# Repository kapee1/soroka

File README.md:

# soroka - DIY-Friendly 40% keyboard

### Build guide [[EN]](https://github.com/kapee1/soroka/blob/main/build%20guides/Soroka%20v2%20Build%20guide%20%5BEN%5D.md) | [[RU]](https://github.com/kapee1/soroka/blob/main/build%20guides/Soroka%20v2%20Build%20guide%20%5BRU%5D.md)

__Parts for v1 and v2 are not compatible!__

### Main features:

* Easy to build. Great for soldering practice.
* Supports all cyrillic symbols in base layer.
* Compatible with most base-kit keycap sets. No 40s addons needed.
* Optional Panasonic EVQWGD001 or EC-11 encoder
* Plate also optional. You can build keyboard without a plate to reduce cost.
* Variable bottom-row with a 3u spacebars support.
* Customizable magnet panels
* VIAL/QMK/[ZMK Firmware](https://github.com/aroum/zmk-soroka) by [aroum](https://github.com/aroum)
* *NEW!* Hotswap PCB (untested, but should be fine). Hotswap PCB uses different diodes. Please check the BOM file at the end of this README file.

### Layout:

### Sizes:

## Hotswap PCB BOM (Be careful, it's still untested!)
| Part     | Quantity |
|----------|----------|
| Soroka PCB (HS)   | 1   | 
| RP2040-Zero (unsoldered pins) | 1   |
| Any MX Hotswap Sockets | 52   |
| BAT54C, SOT-23 Diodes  |  27 | 
| Panasonic EVQWGD001 (optional) or EC-11 Encoder | 1   |  

## Soldered PCB BOM
| Part     | Quantity |
|----------|----------|
| Soroka PCB (Soledered)   | 1   | 
| RP2040-Zero (unsoldered pins) | 1   | 
| 1N4148w SOD-123 Diodes        | 50  | 
| Panasonic EVQWGD001 (optional) or EC-11 Encoder | 1   |  

## Assembly BOM:
| Part     | Quantity |
|----------|----------|
| Soroka PCB (Soldered or Hotswap)   | 1   | 
| Soroka Plate (Optional)       | 1   | 
| Soroka Case                   | 1   | 
| Soroka Panel                  | 1   | 
| Soroka Spacer                 | 1   | 
| Oval feets 22x4x1.5mm         | 4   |  
| Silicone washers 2x5x1        | 9   |
| M2 x 4mm Screws               | 13  |  
| M2 Inserts 3mm (OD3.2)        | 13  |  
| Round magnets 3x1 mm          | 8   | 

In case of cover with screws, you don't need spacer and magnets, but you will need:

| Part     | Quantity |
|----------|----------|
| M2 x 5 mm Screws                       | 8  |  
| M2 Brass Standoffs Female-Female 11 mm | 4  |

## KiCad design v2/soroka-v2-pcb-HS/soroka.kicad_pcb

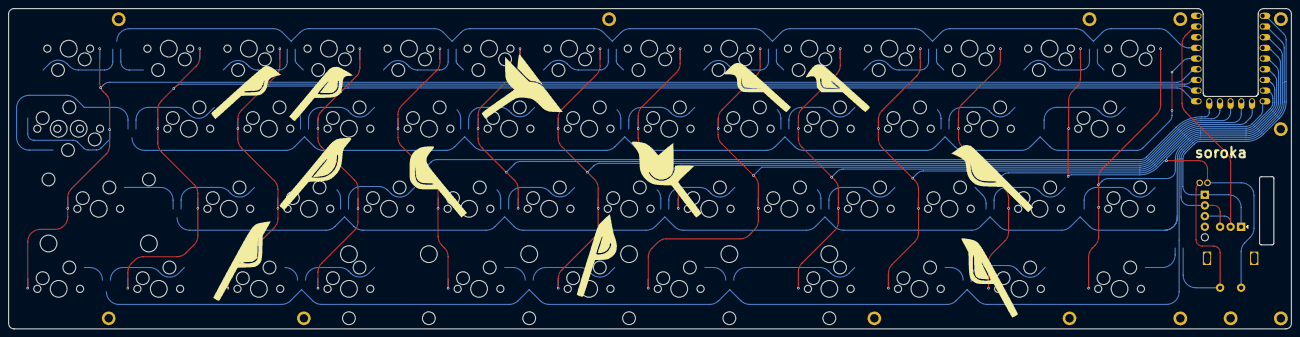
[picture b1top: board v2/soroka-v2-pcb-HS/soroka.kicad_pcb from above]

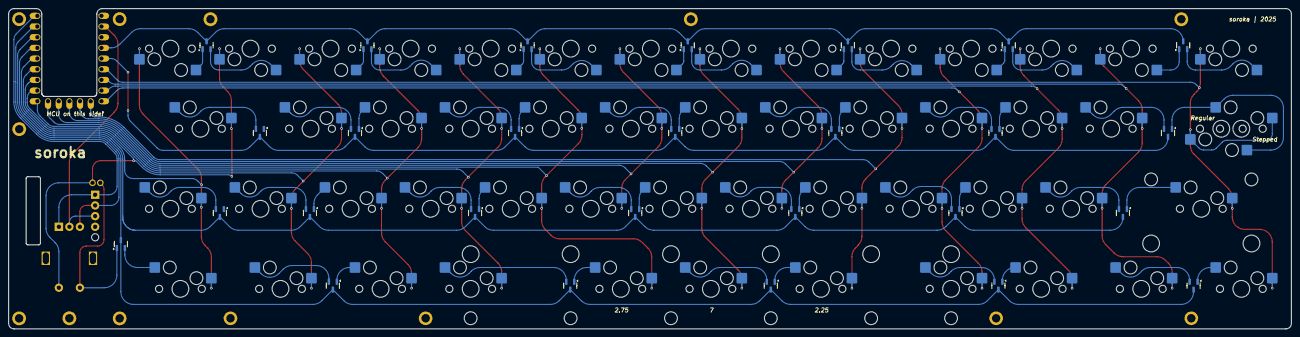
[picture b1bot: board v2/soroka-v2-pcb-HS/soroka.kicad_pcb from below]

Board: 2 copper layers, 305.2 x 76.2 mm, 83 parts (27 on the bottom side), 73 nets.

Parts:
D1, D2, D3, D4, D5, D6, D7, D8, D9, D10, D11, D12, D13, D14, D15, D16, D17, D18, D19, D20, D21, D22, D23, D24, D25, D26, D27: BAT54C; SOT-23
MP: (no value)
RZ1: RP2040-Zero; MCU_rp2040-zero-tht
SW1: MX150H
SW2, SW3, SW4, SW5, SW6, SW7, SW8, SW9, SW10, SW11, SW12, SW13, SW14, SW16, SW17, SW18, SW19, SW20, SW21, SW22, SW23, SW24, SW25, SW26, SW29, SW30, SW31, SW32, SW33, SW34, SW35, SW36, SW37, SW38, SW45, SW50: MXSwitch; MX100H
SW15: Normal; MX125H
SW27: MX175H
SW28: MX225R; MX225H
SW39: 1.25u; MX125H
SW41: 1u; MX100H
SW42, SW43, SW44, SW51, SW52, SW53: MXH125; MX125H
SW46: Stepped; MX175H
SW47: 2.25u; MX225HR
SW48: 7u; MX700HR
SW54: 2.75u; MX275HR
SW55: RotaryEncoder_Switch; RotaryEncoder_Alps_EC11E-Switch_Vertical_H20mm
SW56: RotaryEncoder_Switch; EVQWGD001

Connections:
COL0: RZ1.18 (GP27), SW1.2 (Row), SW15.2 (Row), SW28.2 (Row), SW42.2 (Row), SW46.2 (Row)
COL1: RZ1.17 (GP26), SW2.2 (Row), SW16.2 (Row), SW29.2 (Row), SW43.2 (Row)
COL2: RZ1.16 (GP15), SW3.2 (Row), SW17.2 (Row), SW30.2 (Row), SW44.2 (Row)
COL3: RZ1.15 (GP14), SW4.2 (Row), SW18.2 (Row), SW31.2 (Row), SW45.2 (Row)
COL4: RZ1.14 (GP13), SW5.2 (Row), SW19.2 (Row), SW32.2 (Row), SW47.2 (Row)
COL5: RZ1.13 (GP12), SW6.2 (Row), SW20.2 (Row), SW33.2 (Row)
COL6: RZ1.12 (GP11), SW7.2 (Row), SW21.2 (Row), SW34.2 (Row), SW48.2 (Row)
COL7: RZ1.11 (GP10), SW8.2 (Row), SW22.2 (Row), SW35.2 (Row)
COL8: RZ1.10 (GP9), SW9.2 (Row), SW23.2 (Row), SW36.2 (Row), SW54.2 (Row)
COL9: RZ1.9 (GP8), SW10.2 (Row), SW24.2 (Row), SW37.2 (Row), SW50.2 (Row)
COL10: RZ1.8 (GP7), SW11.2 (Row), SW25.2 (Row), SW38.2 (Row), SW51.2 (Row)
COL11: RZ1.7 (GP6), SW12.2 (Row), SW26.2 (Row), SW39.2 (Row), SW52.2 (Row)
COL12: RZ1.6 (GP5), SW13.2 (Row), SW27.2 (Row), SW55.S2, SW56.S2
COL13: RZ1.5 (GP4), SW14.2 (Row), SW41.2 (Row), SW53.2 (Row)
ENC_CCW: RZ1.1 (GP0), SW55.A, SW56.A
ENC_CW: RZ1.2 (GP1), SW55.B, SW56.B
GND: RZ1.22 (GND), SW55.C, SW56.C
unnamed: D24.1, SW55.S1, SW56.S1
unnamed: D1.2, SW1.1 (Col)
unnamed: D1.1, SW2.1 (Col)
unnamed: D2.2, SW3.1 (Col)
unnamed: D2.1, SW4.1 (Col)
unnamed: D3.2, SW5.1 (Col)
unnamed: D3.1, SW6.1 (Col)
unnamed: D4.2, SW7.1 (Col)
unnamed: D4.1, SW8.1 (Col)
unnamed: D5.2, SW9.1 (Col)
unnamed: D5.1, SW10.1 (Col)
unnamed: D6.2, SW11.1 (Col)
unnamed: D6.1, SW12.1 (Col)
unnamed: D7.2, SW13.1 (Col)
unnamed: D7.1, SW14.1 (Col)
unnamed: D8.1, SW15.1 (Col), SW46.1 (Col)
unnamed: D8.2, SW16.1 (Col)
unnamed: D9.1, SW17.1 (Col)
unnamed: D9.2, SW18.1 (Col)
unnamed: D10.1, SW19.1 (Col)
unnamed: D10.2, SW20.1 (Col)
unnamed: D11.1, SW21.1 (Col)
unnamed: D11.2, SW22.1 (Col)
unnamed: D12.1, SW23.1 (Col)
unnamed: D12.2, SW24.1 (Col)
unnamed: D13.1, SW25.1 (Col)
unnamed: D13.2, SW26.1 (Col)
unnamed: D14.2, SW27.1 (Col)
unnamed: D15.1, SW28.1 (Col)
unnamed: D15.2, SW29.1 (Col)
unnamed: D16.1, SW30.1 (Col)
unnamed: D16.2, SW31.1 (Col)
unnamed: D17.1, SW32.1 (Col)
unnamed: D17.2, SW33.1 (Col)
unnamed: D18.1, SW34.1 (Col)
unnamed: D18.2, SW35.1 (Col)
unnamed: D19.1, SW36.1 (Col)
unnamed: D19.2, SW37.1 (Col)
unnamed: D20.1, SW38.1 (Col)
unnamed: D20.2, SW39.1 (Col)
unnamed: D21.2, SW41.1 (Col)
unnamed: D22.1, SW42.1 (Col)
unnamed: D22.2, SW43.1 (Col)
unnamed: D23.1, SW44.1 (Col)
unnamed: D23.2, SW45.1 (Col)
unnamed: D27.1, SW47.1 (Col)
unnamed: D27.2, SW48.1 (Col)
unnamed: D26.2, SW50.1 (Col)
unnamed: D25.1, SW51.1 (Col)
unnamed: D25.2, SW52.1 (Col)
unnamed: D24.2, SW53.1 (Col)
unnamed: D26.1, SW54.1 (Col)
ROW0: D1.3, D2.3, D3.3, D4.3, D5.3, D6.3, D7.3, RZ1.20 (GP29)
ROW1: D8.3, D9.3, D10.3, D11.3, D12.3, D13.3, D14.3, RZ1.19 (GP28)
ROW2: D15.3, D16.3, D17.3, D18.3, D19.3, D20.3, D21.3, RZ1.4 (GP3)
ROW3: D22.3, D23.3, D24.3, D25.3, D26.3, D27.3, RZ1.3 (GP2)

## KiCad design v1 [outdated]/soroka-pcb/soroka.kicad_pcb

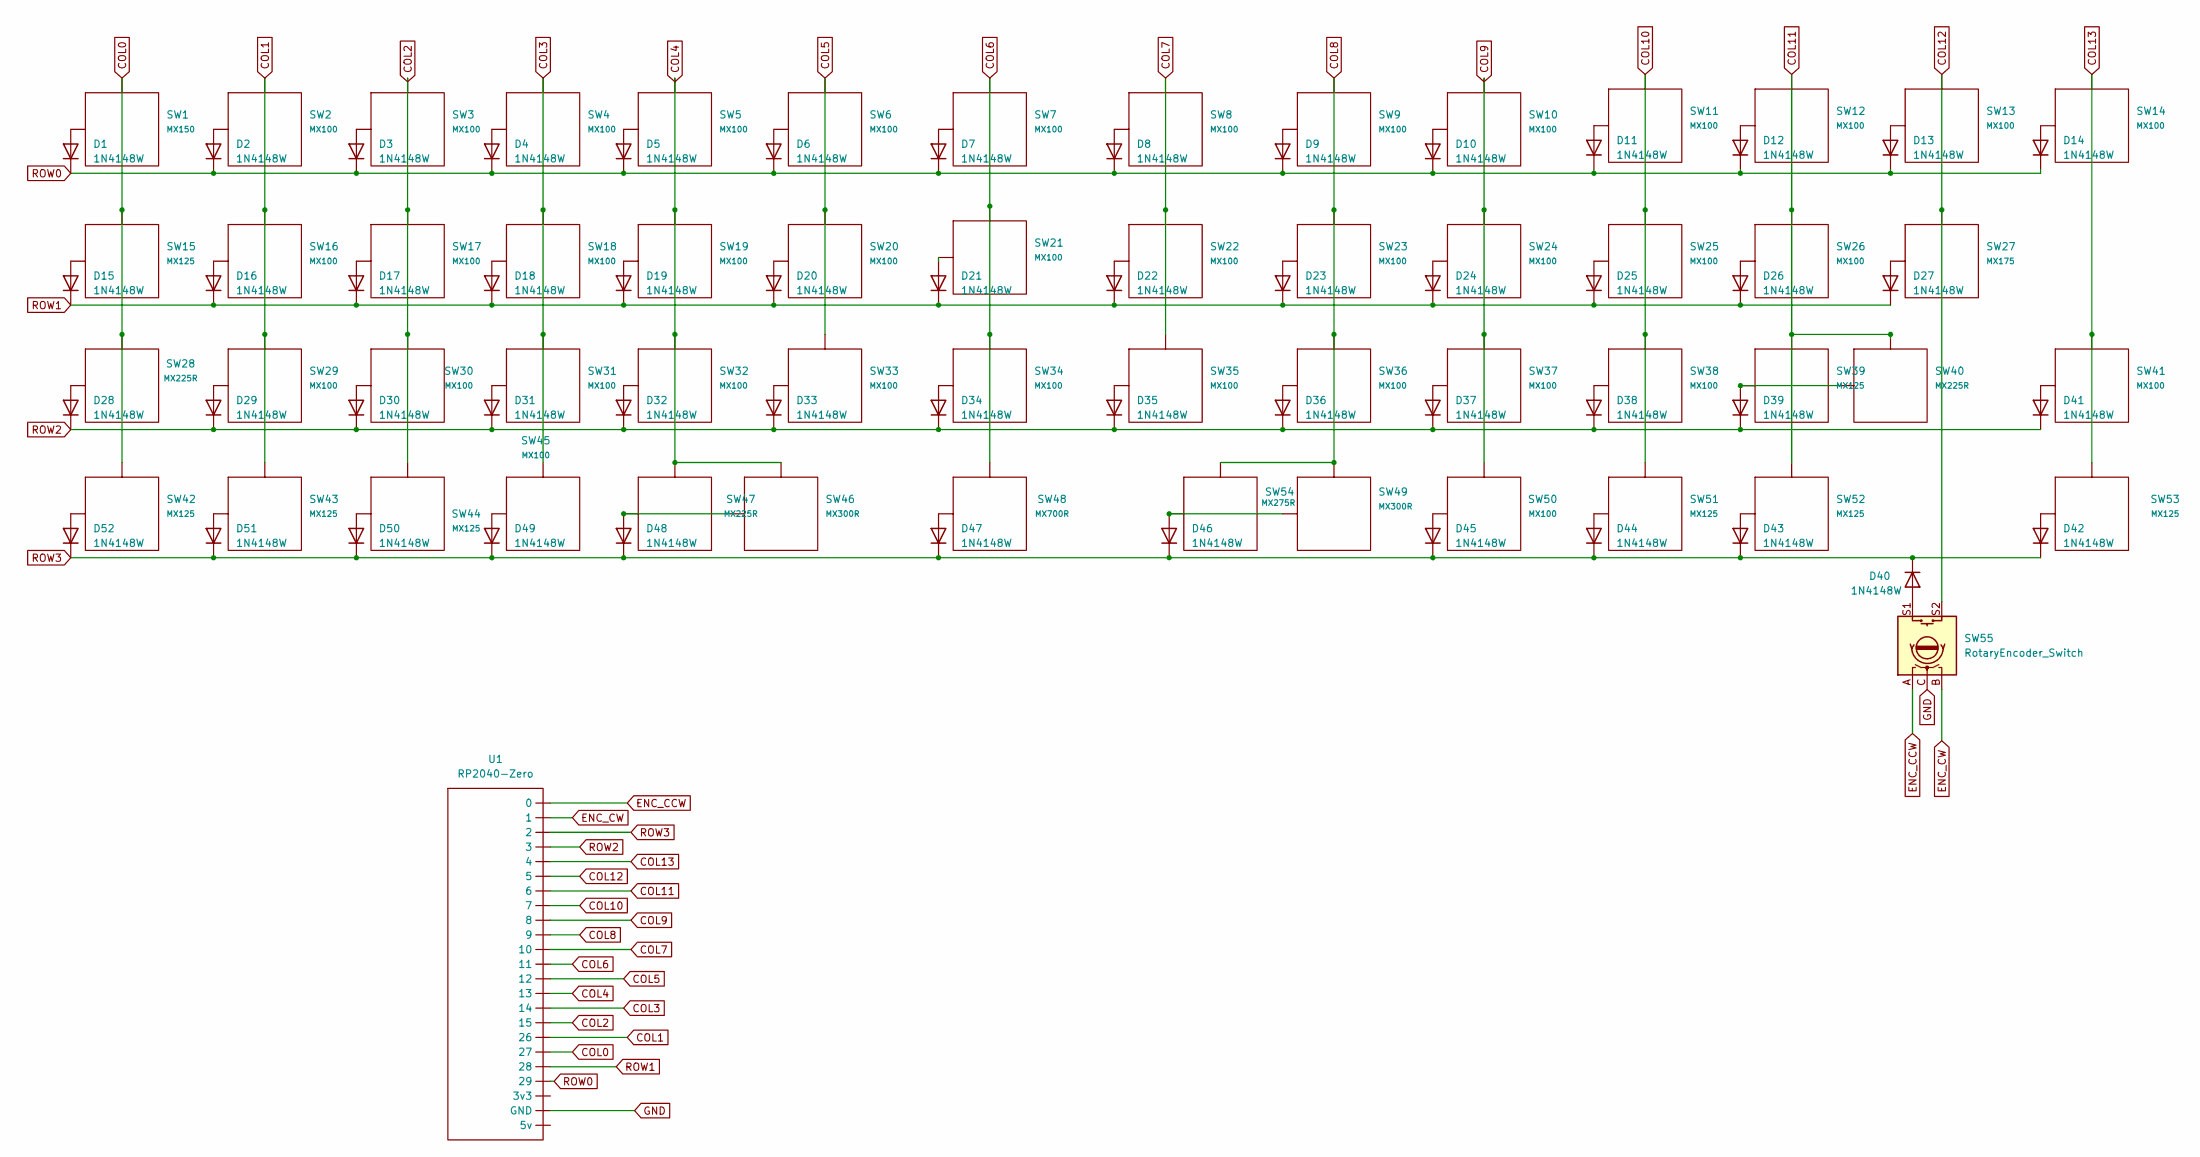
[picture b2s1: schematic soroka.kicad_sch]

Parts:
D1, D2, D3, D4, D5, D6, D7, D8, D9, D10, D11, D12, D13, D14, D15, D16, D17, D18, D19, D20, D21, D22, D23, D24, D25, D26, D27, D28, D29, D30, D31, D32, D33, D34, D35, D36, D37, D38, D39, D40, D41, D42, D43, D44, D45, D46, D47, D48, D49, D50, D51, D52: 1N4148W; D_SOD-123
SW1: MX150
SW2, SW3, SW4, SW5, SW6, SW7, SW8, SW9, SW10, SW11, SW12, SW13, SW14, SW16, SW17, SW18, SW19, SW20, SW21, SW22, SW23, SW24, SW25, SW26, SW29, SW30, SW31, SW32, SW33, SW34, SW35, SW36, SW37, SW38, SW41, SW45, SW50: MX100
SW15, SW39, SW42, SW43, SW44, SW51, SW52, SW53: MX125
SW27: MX175
SW28, SW40: MX225R; MX225
SW46, SW49: MX300R
SW47: MX225R
SW48: MX700R
SW54: MX275R
SW55: RotaryEncoder_Switch; RotaryEncoder_Alps_EC11E-Switch_Vertical_H20mm
U1: RP2040-Zero; MCU_rp2040-zero-smd

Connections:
COL0: SW1.2 (Row), SW15.2 (Row), SW28.2 (Row), SW42.2 (Row), U1.27; also elsewhere on the board
COL1: SW2.2 (Row), SW16.2 (Row), SW29.2 (Row), SW43.2 (Row), U1.26
COL2: SW3.2 (Row), SW17.2 (Row), SW30.2 (Row), SW44.2 (Row), U1.15
COL3: SW4.2 (Row), SW18.2 (Row), SW31.2 (Row), SW45.2 (Row), U1.14
COL4: SW5.2 (Row), SW19.2 (Row), SW32.2 (Row), SW46.2 (Row), SW47.2 (Row), U1.13
COL5: SW6.2 (Row), SW20.2 (Row), SW33.2 (Row), U1.12
COL6: SW7.2 (Row), SW21.2 (Row), SW34.2 (Row), SW48.2 (Row), U1.11
COL7: SW8.2 (Row), SW22.2 (Row), SW35.2 (Row), U1.10
COL8: SW9.2 (Row), SW23.2 (Row), SW36.2 (Row), SW49.2 (Row), SW54.2 (Row), U1.9
COL9: SW10.2 (Row), SW24.2 (Row), SW37.2 (Row), SW50.2 (Row), U1.8
COL10: SW11.2 (Row), SW25.2 (Row), SW38.2 (Row), SW51.2 (Row), U1.7
COL11: SW12.2 (Row), SW26.2 (Row), SW39.2 (Row), SW40.2 (Row), SW52.2 (Row), U1.6
COL12: SW13.2 (Row), SW27.2 (Row), SW55.S2, U1.5
COL13: SW14.2 (Row), SW41.2 (Row), SW53.2 (Row), U1.4
ENC_CCW: SW55.A, U1.0
ENC_CW: SW55.B, U1.1
GND: SW55.C, U1.GND
unnamed: D1.2 (A), SW1.1 (Col)
unnamed: D2.2 (A), SW2.1 (Col)
unnamed: D3.2 (A), SW3.1 (Col)
unnamed: D4.2 (A), SW4.1 (Col)
unnamed: D5.2 (A), SW5.1 (Col)
unnamed: D6.2 (A), SW6.1 (Col)
unnamed: D7.2 (A), SW7.1 (Col)
unnamed: D8.2 (A), SW8.1 (Col)
unnamed: D9.2 (A), SW9.1 (Col)
unnamed: D10.2 (A), SW10.1 (Col)
unnamed: D11.2 (A), SW11.1 (Col)
unnamed: D12.2 (A), SW12.1 (Col)
unnamed: D13.2 (A), SW13.1 (Col)
unnamed: D14.2 (A), SW14.1 (Col)
unnamed 31: D15.2 (A), SW15.1 (Col); also elsewhere on the board
unnamed: D16.2 (A), SW16.1 (Col)
unnamed: D17.2 (A), SW17.1 (Col)
unnamed: D18.2 (A), SW18.1 (Col)
unnamed: D19.2 (A), SW19.1 (Col)
unnamed: D20.2 (A), SW20.1 (Col)
unnamed: D21.2 (A), SW21.1 (Col)
unnamed: D22.2 (A), SW22.1 (Col)
unnamed: D23.2 (A), SW23.1 (Col)
unnamed: D24.2 (A), SW24.1 (Col)
unnamed: D25.2 (A), SW25.1 (Col)
unnamed: D26.2 (A), SW26.1 (Col)
unnamed: D27.2 (A), SW27.1 (Col)
unnamed: D28.2 (A), SW28.1 (Col)
unnamed: D29.2 (A), SW29.1 (Col)
unnamed: D30.2 (A), SW30.1 (Col)
unnamed: D31.2 (A), SW31.1 (Col)
unnamed: D32.2 (A), SW32.1 (Col)
unnamed: D33.2 (A), SW33.1 (Col)
unnamed: D34.2 (A), SW34.1 (Col)
unnamed: D35.2 (A), SW35.1 (Col)
unnamed: D36.2 (A), SW36.1 (Col)
unnamed: D37.2 (A), SW37.1 (Col)
unnamed: D38.2 (A), SW38.1 (Col)
unnamed: D39.2 (A), SW39.1 (Col), SW40.1 (Col)
unnamed: D40.2 (A), SW55.S1
unnamed: D41.2 (A), SW41.1 (Col)
unnamed: D42.2 (A), SW53.1 (Col)
unnamed: D43.2 (A), SW52.1 (Col)
unnamed: D44.2 (A), SW51.1 (Col)
unnamed: D45.2 (A), SW50.1 (Col)
unnamed: D46.2 (A), SW49.1 (Col), SW54.1 (Col)
unnamed: D47.2 (A), SW48.1 (Col)
unnamed: D48.2 (A), SW46.1 (Col), SW47.1 (Col)
unnamed: D49.2 (A), SW45.1 (Col)
unnamed: D50.2 (A), SW44.1 (Col)
unnamed: D51.2 (A), SW43.1 (Col)
unnamed: D52.2 (A), SW42.1 (Col)
ROW0: D1.1 (K), D2.1 (K), D3.1 (K), D4.1 (K), D5.1 (K), D6.1 (K), D7.1 (K), D8.1 (K), D9.1 (K), D10.1 (K), D11.1 (K), D12.1 (K), D13.1 (K), D14.1 (K), U1.29
ROW1: D15.1 (K), D16.1 (K), D17.1 (K), D18.1 (K), D19.1 (K), D20.1 (K), D21.1 (K), D22.1 (K), D23.1 (K), D24.1 (K), D25.1 (K), D26.1 (K), D27.1 (K), U1.28
ROW2: D28.1 (K), D29.1 (K), D30.1 (K), D31.1 (K), D32.1 (K), D33.1 (K), D34.1 (K), D35.1 (K), D36.1 (K), D37.1 (K), D38.1 (K), D39.1 (K), D41.1 (K), U1.3
ROW3: D40.1 (K), D42.1 (K), D43.1 (K), D44.1 (K), D45.1 (K), D46.1 (K), D47.1 (K), D48.1 (K), D49.1 (K), D50.1 (K), D51.1 (K), D52.1 (K), U1.2

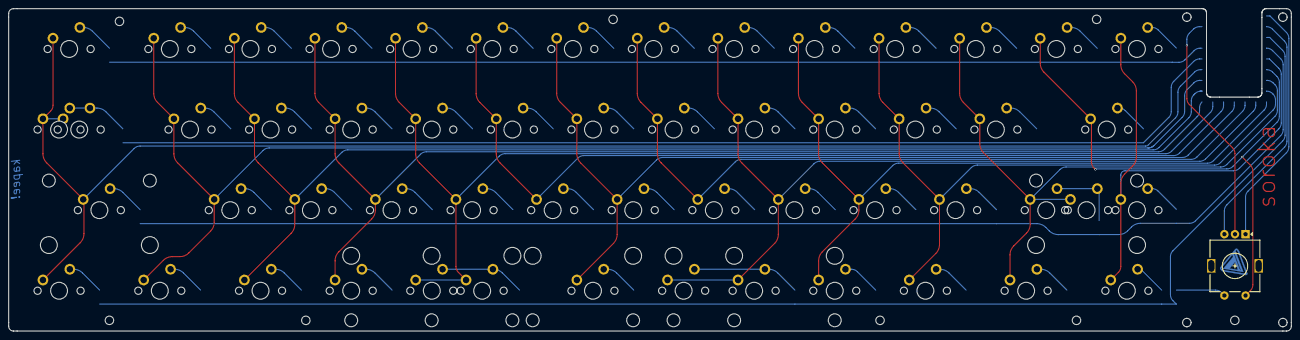
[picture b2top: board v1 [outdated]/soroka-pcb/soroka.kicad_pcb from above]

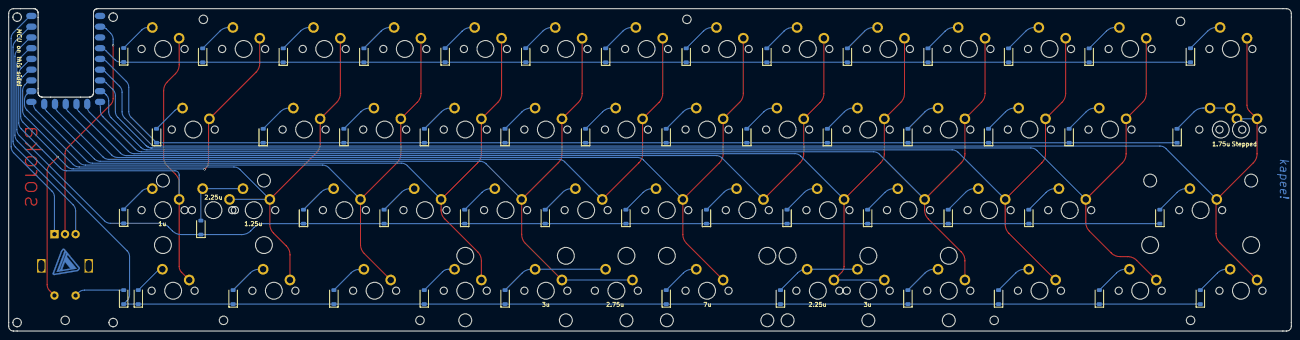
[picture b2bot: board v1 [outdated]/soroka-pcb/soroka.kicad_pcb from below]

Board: 2 copper layers, 303.2 x 76.2 mm, 109 parts (54 on the bottom side), 73 nets.

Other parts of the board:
SW55#2: 1.75u; MX175

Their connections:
COL0: SW55#2.2; also elsewhere on the board
unnamed 31: SW55#2.1; also elsewhere on the board

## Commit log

2024-01-14 added pcb, plate and case files
2024-01-14 added production files
2024-01-15 fixed typo and created new production files
2024-01-19 added 4 variant of right side panels
2024-01-22 fixed stabs cutouts
2024-01-22 added vial firmware
2024-01-29 added 6-degree case
2024-02-01 updated keymaps
2024-08-27 initial commit for v2
2024-08-27 added v2 files
2024-09-19 sorted photos
2024-09-23 added RU build guide
2024-09-23 added EN build guide
2025-04-13 added roundings for evq panels and a new panel
2025-04-13 rename folder
2025-05-15 initial commit for HS pcb
2025-05-26 added untested hotswap PCB
2025-10-19 Fix typo in PCB description in README
